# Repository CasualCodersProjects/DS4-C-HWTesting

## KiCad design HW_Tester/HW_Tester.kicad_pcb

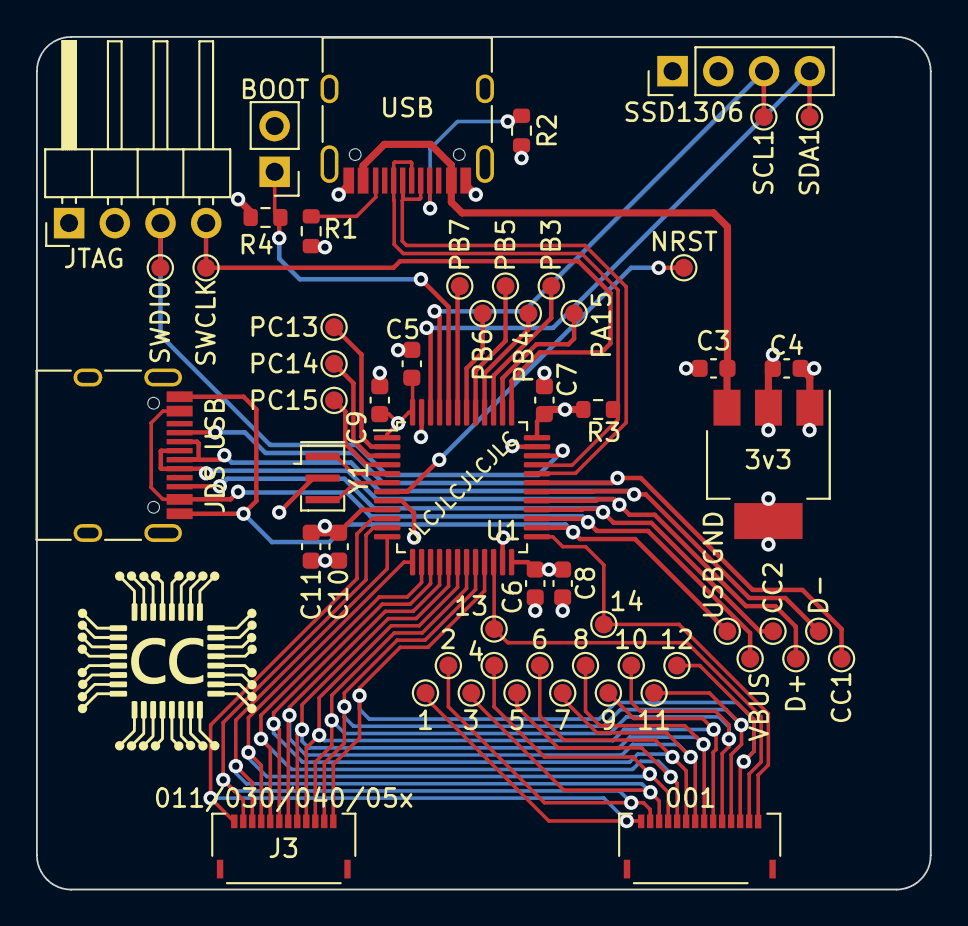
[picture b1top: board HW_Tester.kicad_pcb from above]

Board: 4 copper layers, 49.7 x 47.4 mm, 58 parts (0 on the bottom side), 44 nets.

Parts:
1, 2, 3, 4, 5, 6, 7, 8, 9, 10, 11, 12, 13, 14: TestPoint; TestPoint_Pad_D1.0mm
3v3: AMS1117-3.3; SOT-223-3_TabPin2
BOOT: Boot Jumper; PinHeader_1x02_P2.54mm_Vertical
C3, C4: C; C_0603_1608Metric
C5, C6, C7, C8: 100n; C_0603_1608Metric
C9: 4.7u; C_0603_1608Metric
C10: 10nf; C_0603_1608Metric
C11: 1u; C_0603_1608Metric
CC1, CC2: TestPoint; TestPoint_Pad_D1.0mm
D+: TestPoint; TestPoint_Pad_D1.0mm
D-: TestPoint; TestPoint_Pad_D1.0mm
Ge: LOGO; CC Logo 10mm 6.0
J3: 011/030/040/05x; 503480-1200
J4: 001; 503480-1400
JDS USB: JDS USB; USB_C_Receptacle_HRO_TYPE-C-31-M-12
JTAG: JTAG; PinHeader_1x04_P2.54mm_Horizontal
NRST: TestPoint; TestPoint_Pad_D1.0mm
PA15: TestPoint; TestPoint_Pad_D1.0mm
PB3, PB4, PB5, PB6, PB7: TestPoint; TestPoint_Pad_D1.0mm
PC13, PC14, PC15: TestPoint; TestPoint_Pad_D1.0mm
R1, R2: 5.1k; R_0603_1608Metric
R3: 1.5k; R_0603_1608Metric
R4: 10k; R_0603_1608Metric
SCL1: TestPoint; TestPoint_Pad_D1.0mm
SDA1: TestPoint; TestPoint_Pad_D1.0mm
SSD1306: SSD1306; PinHeader_1x04_P2.54mm_Vertical
SWCLK: TestPoint; TestPoint_Pad_D1.0mm
SWDIO: TestPoint; TestPoint_Pad_D1.0mm
U1: STM32F303CBTx; LQFP-48_7x7mm_P0.5mm
USB: USB C Power; USB_C_Receptacle_HRO_TYPE-C-31-M-12
USBGND: TestPoint; TestPoint_Pad_D1.0mm
VBUS: TestPoint; TestPoint_Pad_D1.0mm
Y1: Resonator; Resonator_SMD_Murata_CSTxExxV-3Pin_3.0x1.1mm

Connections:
+3V3: 3v3.2 (VO), BOOT.2, C4.1, C5.1, C6.1, C7.1, C8.1, C9.1, C10.1, C11.1, JTAG.1, R3.1, SSD1306.2, U1.1 (VBAT), U1.9 (VDDA), U1.24 (VDD), U1.36 (VDD), U1.48 (VDD)
/R+: U1.5 (PF0), Y1.1
/R-: U1.6 (PF1), Y1.3
ADC1_IN1: 1.1, J3.1, J4.1, U1.10 (PA0)
ADC1_IN2: 2.1, J3.2, J4.2, U1.11 (PA1)
ADC2_IN12: 11.1, J3.11, J4.11, U1.20 (PB2)
ADC3_IN1: 10.1, J3.10, J4.10, U1.19 (PB1)
ADC3_IN12: 9.1, J3.9, J4.9, U1.18 (PB0)
BOOT: BOOT.1, R4.1, U1.44 (BOOT0)
D+: R3.2, U1.33 (PA12), USB.A6 (D+), USB.B6 (D+)
D-: U1.32 (PA11), USB.A7 (D-), USB.B7 (D-)
GND: 3v3.1 (GND), C3.2, C4.2, C5.2, C6.2, C7.2, C8.2, C9.2, C10.2, C11.2, JTAG.2, R1.2, R2.2, R4.2, SSD1306.1, U1.8 (VSSA), U1.23 (VSS), U1.35 (VSS), U1.47 (VSS), USB.A1 (GND), USB.A12 (GND), USB.B1 (GND), USB.B12 (GND), Y1.2
I2C1_SCL/CAN_RX: SCL1.1, SSD1306.3, U1.45 (PB8)
I2C1_SCL/SPI1_NSS/SPI3_NSS/UART2_RX: PA15.1, U1.38 (PA15)
I2C1_SCL/UART1TX: PB6.1, U1.42 (PB6)
I2C1_SDA/CAN_TX: SDA1.1, SSD1306.4, U1.46 (PB9)
I2C1_SDA/UART1_RX: PB7.1, U1.43 (PB7)
I2C2_SCK/ADC3_IN5: JDS USB.A1 (GND), JDS USB.A12 (GND), JDS USB.B1 (GND), JDS USB.B12 (GND), U1.26 (PB13), USBGND.1
I2C2_SCL/UART1_TX: D-.1, JDS USB.A7 (D-), JDS USB.B7 (D-), U1.30 (PA9)
I2C2_SDA/UART1_RX: CC1.1, JDS USB.A5 (CC1), U1.31 (PA10)
NRST: NRST.1, U1.7 (NRST)
unnamed: R2.1, USB.A5 (CC1)
unnamed: R1.1, USB.B5 (CC2)
PA8: D+.1, JDS USB.A6 (D+), JDS USB.B6 (D+), U1.29 (PA8)
PC13: PC13.1, U1.2 (PC13)
PC14: PC14.1, U1.3 (PC14)
PC15: PC15.1, U1.4 (PC15)
SPI1_MISO/ADC2_IN3: 7.1, J3.7, J4.7, U1.16 (PA6)
SPI1_MOSI/ADC2_IN4: 8.1, J3.8, J4.8, U1.17 (PA7)
SPI1_NSS/SPI3_NSS/ADC2_IN1/DAC1_OUT1: 5.1, J3.5, J4.5, U1.14 (PA4)
SPI1_SCK/ADC2_IN2/DAC1_OUT2: 6.1, J3.6, J4.6, U1.15 (PA5)
SPI1_SCK/SPI3_SCK/UART2_TX: PB3.1, U1.39 (PB3)
SPI2_MISO/ADC4_IN4: JDS USB.A4 (VBUS), JDS USB.A9 (VBUS), JDS USB.B4 (VBUS), JDS USB.B9 (VBUS), U1.27 (PB14), VBUS.1
SPI2_MOSI/ADC4_IN5: CC2.1, JDS USB.B5 (CC2), U1.28 (PB15)
SPI2_NSS/ADC4_IN3: 14.1, J4.14, U1.25 (PB12)
SPI3_MISO/SPI1_MISO/UART2_RX: PB4.1, U1.40 (PB4)
SPI3_MOSI/SPI1_MOSI: PB5.1, U1.41 (PB5)
SWCLK-JTCK/I2C1_SDA/UART2_TX: JTAG.4, SWCLK.1, U1.37 (PA14)
SWDIO_JTMS: JTAG.3, SWDIO.1, U1.34 (PA13)
UART2_RX/ADC1_IN4: 4.1, J3.4, J4.4, U1.13 (PA3)
UART2_TX/ADC1_IN3: 3.1, J3.3, J4.3, U1.12 (PA2)
UART3_RX: 13.1, J4.13, U1.22 (PB11)
UART3_TX: 12.1, J3.12, J4.12, U1.21 (PB10)
VCC: 3v3.3 (VI), C3.1, USB.A4 (VBUS), USB.A9 (VBUS), USB.B4 (VBUS), USB.B9 (VBUS)

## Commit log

2022-04-30 Mostly done board. Test pads in progress
2022-04-30 Completed board pending review
2022-04-30 Updated placements, zones, and outline

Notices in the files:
parts and their libraries:
Copyright 2021 Accelerated Designs. All rights reserved.
